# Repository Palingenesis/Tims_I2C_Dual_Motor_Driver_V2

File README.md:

# This is My I2C Dual Motor Driver Version 2  
.png)  
## This is an I2C controlled Dual Motor Driver Board.  
<span style="color: red; font-weight: bold;">This Board supperceeds this one [Tims I2C Dual Motor Driver](https://github.com/Palingenesis/Tims-I2C-Dual-Motor-Driver?tab=readme-ov-file)</span>
### Files are for [KiCAD EDA](https://www.kicad.org/)  
There is <span style="font-size: large;">**"Tims_I2C_Dual_Motor_Driver_V2.kicad_pcb.zip"**</span> file  
* This can be used when **"Plot Files"** asked for at 
<sub></sub> 
when ordering 10 PCBs for $5  
* If you have <span style="font-size: large;">**[KiCAD EDA](https://www.kicad.org/)**</span>,  
<sub></sub>
have a Plugin  that will make things simple to order a PCB,  
just load this project into <span style="font-size: large;">**[KiCAD EDA](https://www.kicad.org/)**</span> install the plugin click the Icon  and it will create all the nesesery files needed and take you to order a PCB 
and compeate the form on 
<sub></sub> 
web site.  

## About  
The board can control two motors with quadratic encoders and a station to set a reference point.  
This is my second I2C Motor Driver, My first worked OK, but The MOSFETS I used where a little temperamental,  
so I decided to make a more robust version.  
This one I decided to control 2 motors from one microcontroller.  
* The main reason for having it control two motors at the same time was that I tried my original motor drivers controlling a tracked vehicle.  
It worked fine with two single motor drivers  but because I was using a web interface to control them there was a delay between turning on/off each motor.  
* I thought having a motor driver that controls two motor at the same time was a better approach.  
  
## The Motor Driver is controlled via the I2C bus.  
* Each board can have its own unique I2C Address.  
* Not using the reserved Addresses over 100 in theory can be attached to one I2C bus. (Addresses 10 to 127 probably) 7-bit Address.  
* The is a system to reset the I2C default address to 0x30.  
* There are two sockets for the I2C to that the boards can be daisy-chained, end to end.  
* There is place for pull-up resistors, depending on muti-board setup or single board setup, these can be enabled/disabled.  

## The Microcontroller is the STM8S103F3
  
* According to the Data Sheet, this can run with 2.95 to 5.5 V operating voltage.  
* Caution should be taken when programming, The ST-Link is 3.3v.  
* I was a little limited for pins and memory, as I am controlling two motors with this. The AI has been reduced, it still has inputs for quadratic encoders and a station, these enable it to know the rotation and position of the motors.  
* I was able to use the current sense from the DRV8876, so the load on the motors can be retrieved from communication via I2C.  
## There are LEDs for diagnostics.  
* Two Yellow LEDs, one for Motor Power and one for VCC.  
* There is a red LED on the SDA line to show activity.  
* For each motor there is a red LED to show a fault, a blue LED to show Motor on and a Green LED to show if motor forward or reverse (on/off).  
## There are Pads for programming the STM8S103F3
* To program the STM8S103F3 will require STMicroelectronics "ST Visual Programmer"  
* STMicroelectronics "ST Visual Programmer" is part of "ST MCU toolset".  
* I have done .s19 file for use with the "ST Visual Programmer".  
* An ST-Link is required.
  
## The Drivers used are DRV8876
  
The DRV8876 is an N-channel H-bridge motor driver, the board has two of these.  
* They have 4.5-V to 37-V operating supply voltage range.  
* 3.5-A Peak. On the board I have put places for Current limit resistors.  
* Supports 1.8-V, 3.3-V, and 5-V logic inputs. (The STM8S103F3 opperates at 2.95 to 5.5 V)  
* On the board the DRV8876 are set to PH/EN Control Mode.  
* The nSleep is fixed High, so no low power mode.  
* I have connected the IPROPI to the STM8S103F3 so current readings can be sensed.  
## There are connections for a Quadratic Encoder for each Motor  
  
The Quadratic Encoder needs to be the A/B type and be the same VCC as the Board.  
* If the Board counts bacwards when the motor runs forward, the two quadratic input need to be swapped.  
* With an encoder attached to a motor, commands can be sent to set the motor to a specific position.  
## There are connections for a Station for each Motor  
* A Station is a place for a switch to be fitted to a project, that when triggerd, will reset the position of the Motor to a known position.  
* There are two settings for the station depending on the direction of the Motor, most switches don't trigger at the same point when turning on and off.  
## Commands  
The Motor Driver Board is controlled by commands on the I2C Bus.  
* The Board can be connected to any microcontroller that has I2C.  
* All commands start with any byte, this is because I have an ESP8266 and they haven't fixed the first data byte issue. When sending data via the I2C on the ESP8266 the first byte gets 0x80 added to it. So my driver ignores the first byte sent. For simplicity I will use '#' as the first character of all commands sent to the Motor Driver.  
* The second byte is the Identifier that tells the driver the type of command. All commands are from the second byte onwards. I should say "char" as all commands are sent as ASCII characters.  
## Global Command 'M'  
* **M1** = Motor A is the current motor that will be adjusted.  
* **M2** = Motor B is the current motor that will be adjusted.  
* **M3** = Motor A and B be adjusted.  
* A global command can be used on its own (preceded with '#') or at the end of other commands (preceded with a space)  
## 'C' Commands (settings):
* **C1** = Sets the Current Position to 0 (zero). Just use **C1**.  
* **C6 B\<value>** = Set: Has a Station Position. **B**oolean = 1 or 0 (true or false).  
* **C7 P\<value>** = Set the Forward Station **P**osition value. value = a 16 bit value, Sets the Station Position while moving Forward.  
* **C8 P\<value>** = Set the Reverse Station **P**osition value. value = a 16 bit value, Sets the Station Position while moving in Reverse.  
* **C10 A\<value>** = Set I2C **A**ddress. value = 1 (0x00) to 127 (0x7F). This is to change the I2C Address of the device.  
* **C13 B\<value>** = Set I2C Speed. **B**oolean; Is it 400k. value = 1 or 0 (true or false). 1 = 400000, 0 = 100000.  
All setting are saved in non volatile memory.  
* No need to apply settings every time power it connected.  
## 'S' Command (Speed):
**S\<Value>** = Set the **S**peed 0 to 1000. This is a PWM value. So 500 would be 50% on 50% off square wave.  
## 'F' Commands (Forward):
* **F0** = Stop. Can just use 'F' as the buffer will be full of zeros.  
* **F1** = Forward at a current Speed.  
* **F1 S\<value>** = Forward at a set Speed.  
## 'R' Commands (Reverse):  
* **R0** = Stop. Can just use 'R' as the buffer will be full of zeros.  
* **R1** = Reverse at a current Speed.  
* **R1** S<value> = Reverse at a set Speed.  
## 'G' Commands (Go to):
* **G0** = **Stop**. Can just use **'G'** as the buffer will be full of zeros.  
* **G1 P\<value> S\<value>** = Move to an absolute **P**osition Forward (Positive) of zero at a **S**peed.  
* **G2 P\<value> S\<value>** = Move to an absolute **P**osition Reverse (Negative) of zero at a **S**peed.  
  
*Settings that set a position are only valid with motors that have a Quadratic Encoder.*  
  
The **'G'** code **P**\<value> can be negative values. So why have **G1** and **G2**?  
* To keep options open.  
* All positions are relative to a zero.  
* When writing your own code to control the Motors you may only have the option of Unsigned Integers.  
* You may want to only use Unsigned Integers to save memory.  

### *Click this image to see a video of it in use.*

## A Typical 4 Motor setup  
  
* One Microcontroller.  
* Two Driver Boards.  
* Four Motors With Quadratic Encoders.  
* Each Motor has a Station to set the the zero position.  
  
  --

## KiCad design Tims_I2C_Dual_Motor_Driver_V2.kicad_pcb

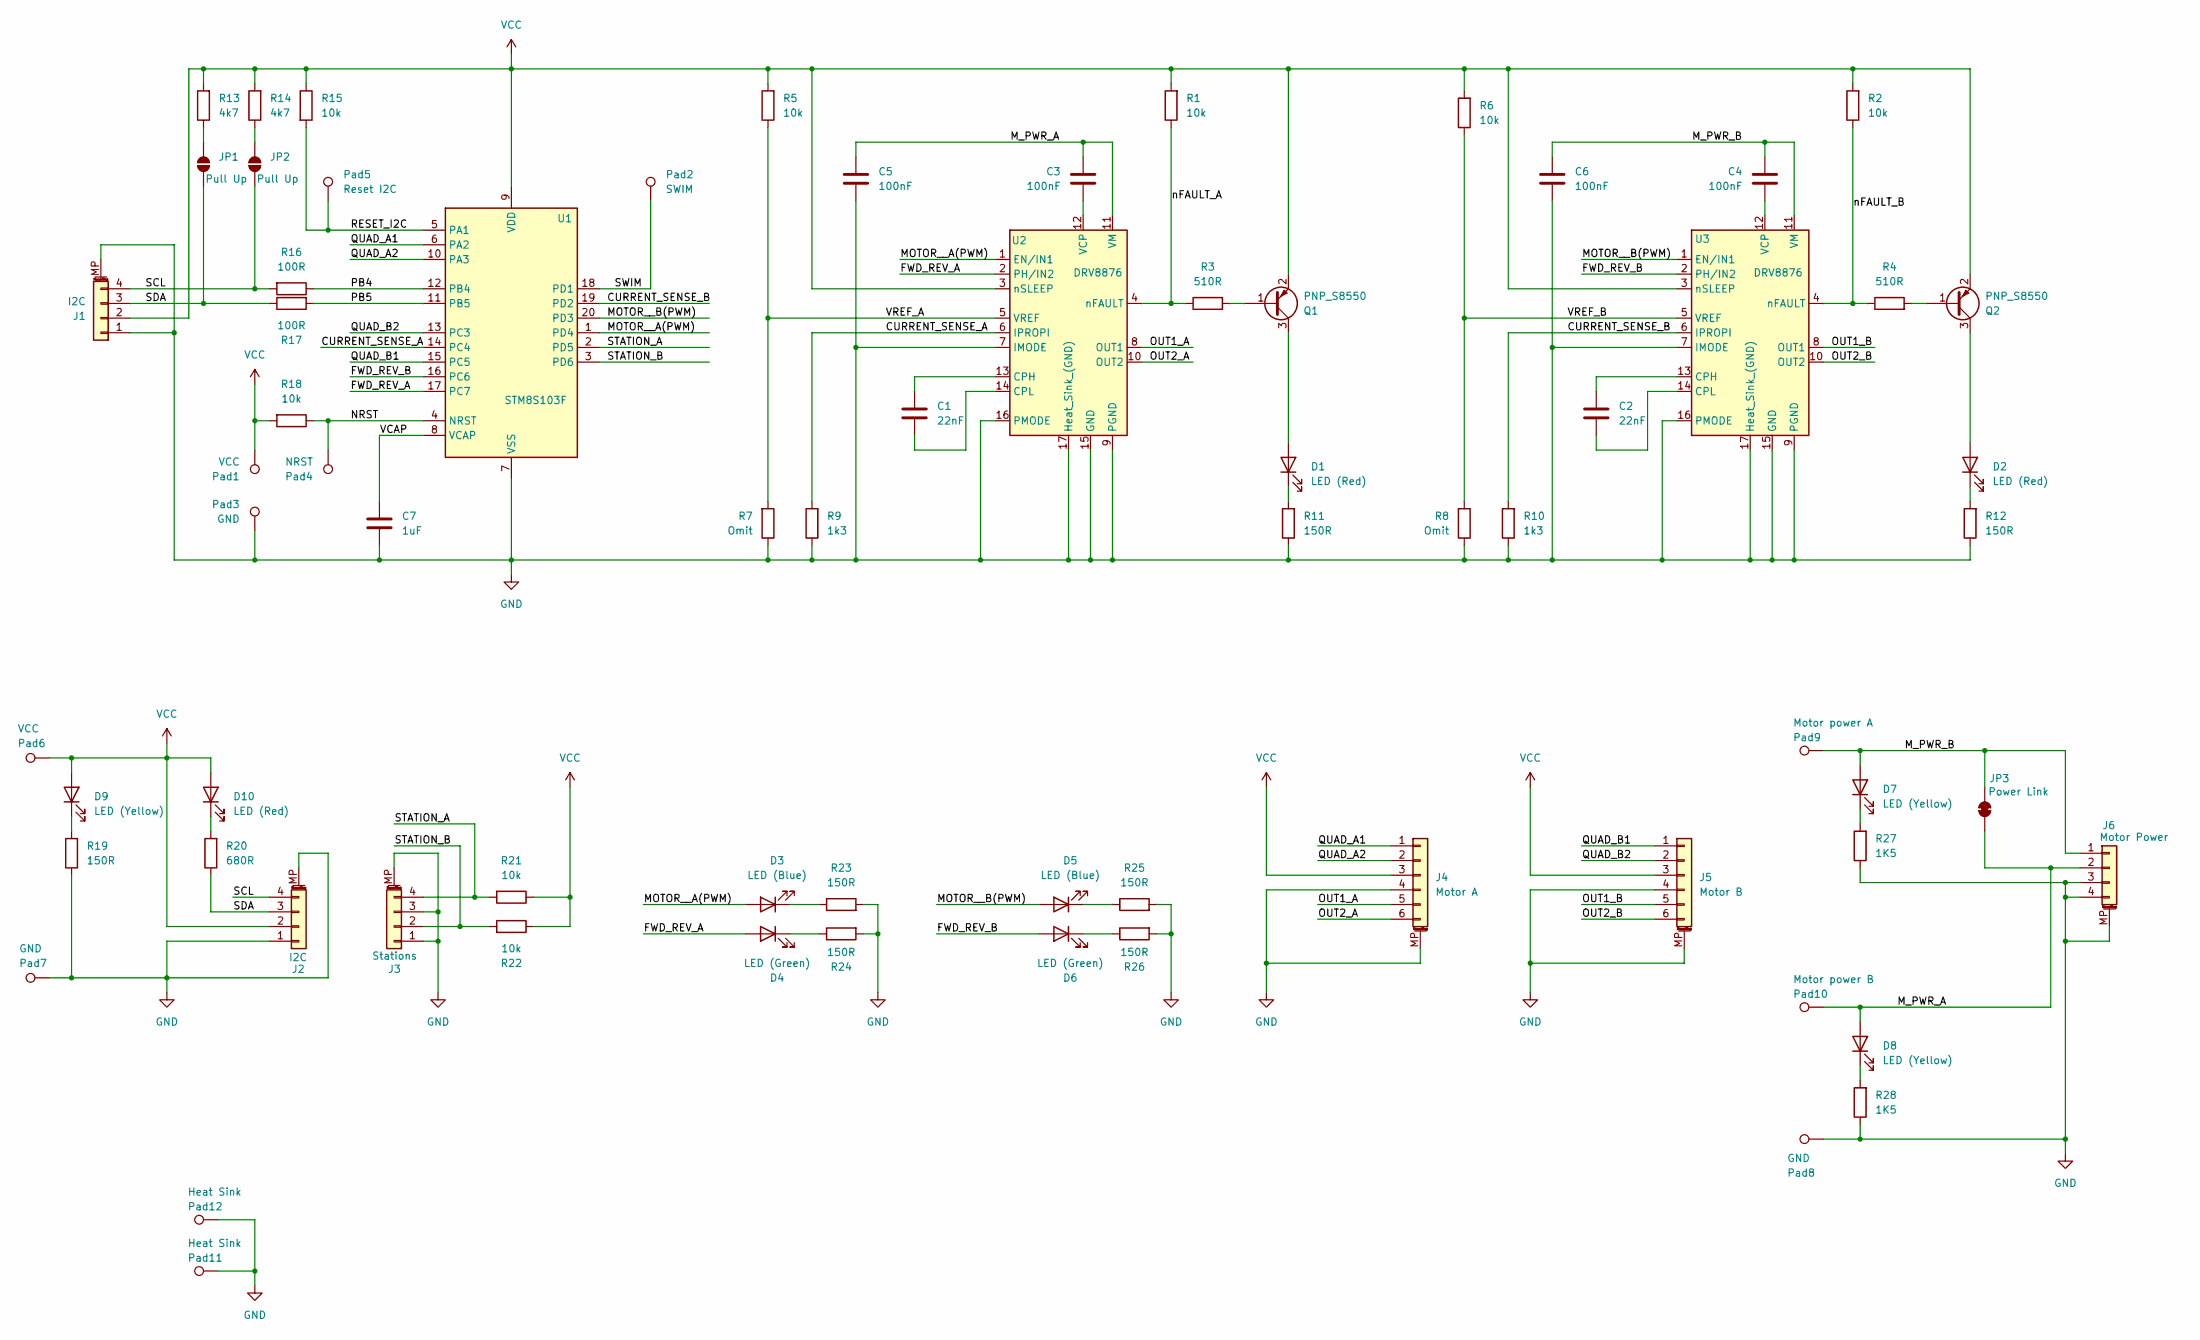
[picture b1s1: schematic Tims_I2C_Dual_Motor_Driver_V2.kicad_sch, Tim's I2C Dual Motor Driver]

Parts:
C1, C2: 22nF; C_0805_2012Metric
C3, C4: 100nF; C_0805_2012Metric
C5, C6: 100nF; C_1206_3216Metric
C7: 1uF; C_0805_2012Metric
D1, D2, D10: LED (Red); LED_0805_2012Metric
D3, D5: LED (Blue); LED_0805_2012Metric
D4, D6: LED (Green); LED_0805_2012Metric
D7, D8, D9: LED (Yellow); LED_0805_2012Metric
J1, J2: I2C; JST_PH_S4B-PH-SM4-TB_1x04-1MP_P2.00mm_Horizontal
J3: Stations; JST_PH_S4B-PH-SM4-TB_1x04-1MP_P2.00mm_Horizontal
J4: Motor A; JST_PH_S6B-PH-SM4-TB_1x06-1MP_P2.00mm_Horizontal
J5: Motor B; JST_PH_S6B-PH-SM4-TB_1x06-1MP_P2.00mm_Horizontal
J6: Motor Power; JST_PH_S4B-PH-SM4-TB_1x04-1MP_P2.00mm_Horizontal
JP1, JP2: Pull Up; SolderJumper-2_P1.3mm_Open_RoundedPad1.0x1.0mm
JP3: Power Link; SolderJumper-2_P1.3mm_Bridged_RoundedPad1.0x1.0mm
Pad1, Pad6: VCC; Wire_Conn
Pad2: SWIM; Wire_Conn
Pad3, Pad7, Pad8: GND; Wire_Conn
Pad4: NRST; Wire_Conn
Pad5: Reset I2C; Wire_Conn
Pad9: Motor power A; Wire_Conn
Pad10: Motor power B; Wire_Conn
Pad11, Pad12: Heat Sink; Wire_Conn
Q1, Q2: PNP_S8550; SOT-23
R1, R2, R5, R6, R15, R18, R21, R22: 10k; R_0805_2012Metric
R3, R4: 510R; R_0805_2012Metric
R7, R8: Omit; R_0805_2012Metric
R9, R10: 1k3; R_0805_2012Metric
R11, R12, R19, R23, R24, R25, R26: 150R; R_0805_2012Metric
R13, R14: 4k7; R_0805_2012Metric
R16, R17: 100R; R_0805_2012Metric
R20: 680R; R_0805_2012Metric
R27, R28: 1K5; R_0805_2012Metric
U1: STM8S103F; TSSOP-20_4.4x6.5mm_P0.65mm
U2, U3: DRV8876; HTSSOP-16-1EP_4.4x5mm_P0.65mm_EP3x3mm

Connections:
/CURRENT_SENSE_A: R9.2, U1.14 (PC4), U2.6 (IPROPI)
/CURRENT_SENSE_B: R10.2, U1.19 (PD2), U3.6 (IPROPI)
/FWD_REV_A: D4.2 (A), U1.17 (PC7), U2.2 (PH/IN2)
/FWD_REV_B: D6.2 (A), U1.16 (PC6), U3.2 (PH/IN2)
/MOTOR__A(PWM): D3.2 (A), U1.1 (PD4), U2.1 (EN/IN1)
/MOTOR__B(PWM): D5.2 (A), U1.20 (PD3), U3.1 (EN/IN1)
/M_PWR_A: C3.2, C5.1, D8.2 (A), J6.2, JP3.1 (A), Pad10.1, U2.11 (VM)
/M_PWR_B: C4.2, C6.1, D7.2 (A), J6.1, JP3.2 (B), Pad9.1, U3.11 (VM)
/NRST: Pad4.1, R18.1, U1.4 (NRST)
/OUT1_A: J4.5, U2.8 (OUT1)
/OUT1_B: J5.5, U3.8 (OUT1)
/OUT2_A: J4.6, U2.10 (OUT2)
/OUT2_B: J5.6, U3.10 (OUT2)
/PB4: R16.1, U1.12 (PB4)
/PB5: R17.2, U1.11 (PB5)
/QUAD_A1: J4.1, U1.6 (PA2)
/QUAD_A2: J4.2, U1.10 (PA3)
/QUAD_B1: J5.1, U1.15 (PC5)
/QUAD_B2: J5.2, U1.13 (PC3)
/RESET_I2C: Pad5.1, R15.2, U1.5 (PA1)
/SCL: J1.4, J2.4, JP2.1 (A), R16.2
/SDA: J1.3, J2.3, JP1.1 (A), R17.1, R20.1
/STATION_A: J3.4, R21.2, U1.2 (PD5)
/STATION_B: J3.2, R22.2, U1.3 (PD6)
/SWIM: Pad2.1, U1.18 (PD1)
/VCAP: C7.1, U1.8 (VCAP)
/VREF_A: R5.1, R7.2, U2.5 (VREF)
/VREF_B: R6.1, R8.2, U3.5 (VREF)
/nFAULT_A: R1.1, R3.1, U2.4 (nFAULT)
/nFAULT_B: R2.1, R4.1, U3.4 (nFAULT)
GND: C5.2, C6.2, C7.2, J1.1, J1.MP (MountPin), J2.1, J2.MP (MountPin), J3.1, J3.3, J3.MP (MountPin), J4.4, J4.MP (MountPin), J5.4, J5.MP (MountPin), J6.3, J6.4, J6.MP (MountPin), Pad3.1, Pad7.1, Pad8.1, Pad11.1, Pad12.1, R7.1, R8.1, R9.1, R10.1, R11.1, R12.1, R19.1, R23.2, R24.2, R25.2, R26.2, R27.1, R28.1, U1.7 (VSS), U2.7 (IMODE), U2.9 (PGND), U2.15 (GND), U2.16 (PMODE), U2.17 (Heat_Sink_(GND)), U3.7 (IMODE), U3.9 (PGND), U3.15 (GND), U3.16 (PMODE), U3.17 (Heat_Sink_(GND))
unnamed: D1.2 (A), Q1.3 (C)
unnamed: D1.1 (K), R11.2
unnamed: D2.2 (A), Q2.3 (C)
unnamed: D2.1 (K), R12.2
unnamed: D3.1 (K), R23.1
unnamed: D4.1 (K), R24.1
unnamed: D5.1 (K), R25.1
unnamed: D6.1 (K), R26.1
unnamed: D7.1 (K), R27.2
unnamed: D8.1 (K), R28.2
unnamed: D9.1 (K), R19.2
unnamed: D10.1 (K), R20.2
unnamed: JP1.2 (B), R13.1
unnamed: JP2.2 (B), R14.1
unnamed: Q1.1 (B), R3.2
unnamed: Q2.1 (B), R4.2
unnamed: C1.1, U2.13 (CPH)
unnamed: C1.2, U2.14 (CPL)
unnamed: C3.1, U2.12 (VCP)
unnamed: C2.1, U3.13 (CPH)
unnamed: C2.2, U3.14 (CPL)
unnamed: C4.1, U3.12 (VCP)
VCC: D9.2 (A), D10.2 (A), J1.2, J2.2, J4.3, J5.3, Pad1.1, Pad6.1, Q1.2 (E), Q2.2 (E), R1.2, R2.2, R5.2, R6.2, R13.2, R14.2, R15.1, R18.2, R21.1, R22.1, U1.9 (VDD), U2.3 (nSLEEP), U3.3 (nSLEEP)

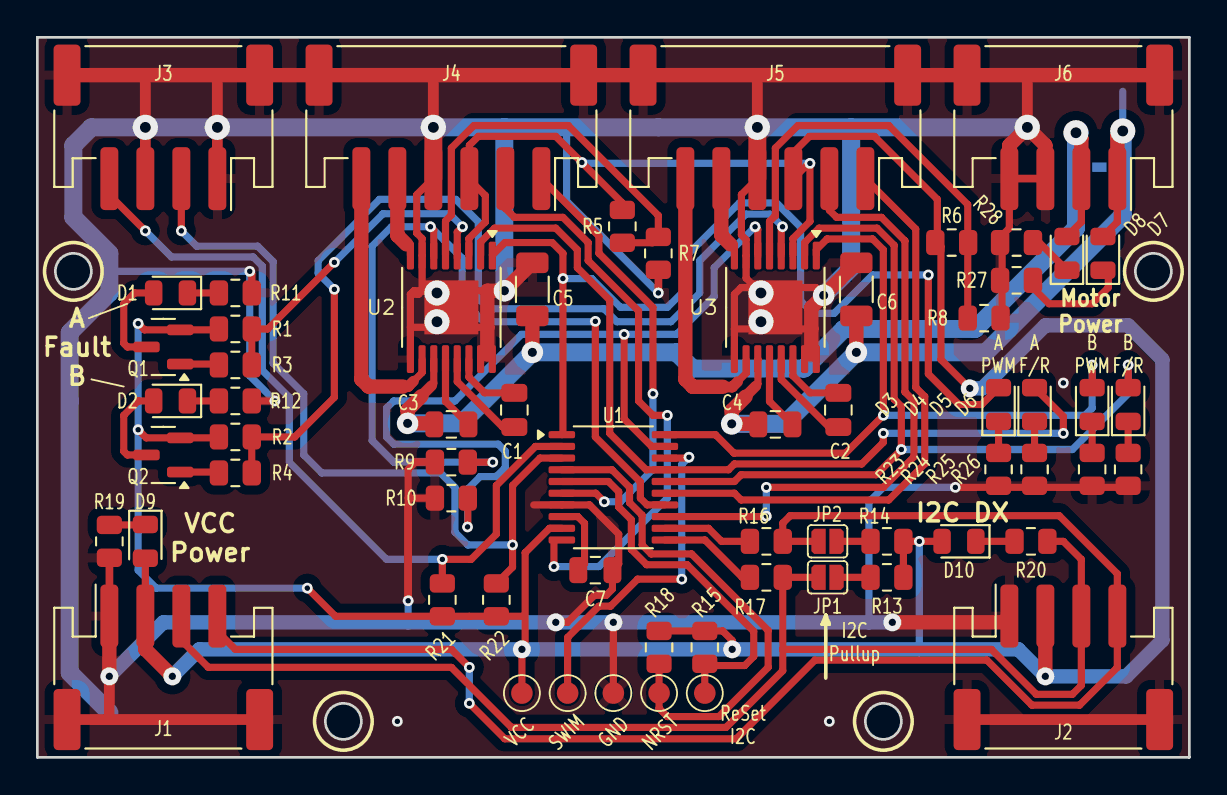
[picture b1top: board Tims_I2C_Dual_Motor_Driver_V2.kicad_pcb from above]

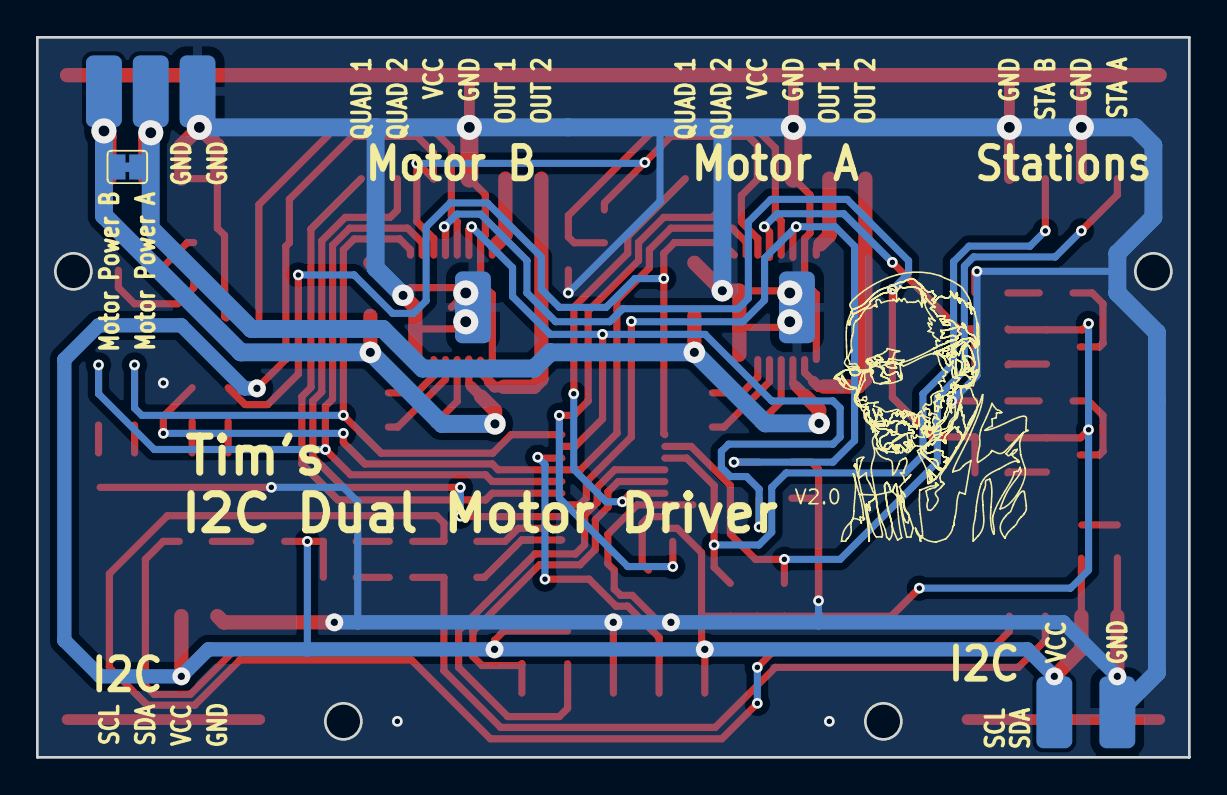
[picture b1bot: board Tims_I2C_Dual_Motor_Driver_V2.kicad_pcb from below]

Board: 2 copper layers, 64.0 x 40.0 mm, 71 parts (8 on the bottom side), 54 nets.

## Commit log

2024-09-30 Add project files.
2025-11-24 Update web
2025-11-24 Added Version 3 Firmware for Version 2 PCB,
2025-11-24 cange MD ot README.
